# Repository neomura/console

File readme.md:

# neomura/console

Circuit design and shell for home console.

| Link                                         | Description                                        |
| -------------------------------------------- | -------------------------------------------------- |
| [License](./license.md)                      | MIT License.                                       |
| [Circuit Design](./circuit-design/readme.md) | KiCad files and assembly instructions for the PCB. |
| [Shell](./shell/readme.md)                   | OpenSCAD modules for the outer shell.              |

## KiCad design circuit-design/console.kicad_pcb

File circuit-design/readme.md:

# [neomura/console](../readme.md)/Circuit Design

| Link                                                                                               | Description                             |
| -------------------------------------------------------------------------------------------------- | --------------------------------------- |
| [console.pro](./console.pro)                                                                       | KiCAD project.                          |
| [console.sch](./console.sch)                                                                       | KiCAD schematic.                        |
| [console.kicad_pcb](./console.kicad_pcb)                                                           | KiCAD PCB layout.                       |
| [Neomura_Console.lib](./Neomura_Console.lib)                                                       | KiCAD symbol for pad connector.         |
| [Neomura_Console.pretty/BS800L.kicad_mod](./Neomura_Console.pretty/BS800L.kicad_mod)               | KiCAD footprint for power/reset switch. |
| [Neomura_Console.pretty/Pad_Connector.kicad_mod](./Neomura_Console.pretty/Pad_Connector.kicad_mod) | KiCAD footprint for pad connector.      |
| [Neomura_Console.pretty/RCA_Jack.kicad_mod](./Neomura_Console.pretty/RCA_Jack.kicad_mod)           | KiCAD footprint for RCA jack.           |

## Bill of materials

Links are included for reference only and are not endorsements.

| Reference   | Description                                             | Model No.         | Link                                                                                                                                                                                               |
| ----------- | ------------------------------------------------------- | ----------------- | -------------------------------------------------------------------------------------------------------------------------------------------------------------------------------------------------- |
| J1          | Cartridge connector (1x15 2.54mm female pin socket)     | Unknown           | [https://www.aliexpress.com/item/33021040052.html?spm=a2g0s.9042311.0.0.65b74c4dMpBmdG](https://www.aliexpress.com/item/33021040052.html?spm=a2g0s.9042311.0.0.65b74c4dMpBmdG)                     |
| J2          | 2.1mm PCB-mount DC power jack                           | Unknown           | [https://www.bitsbox.co.uk/index.php?main_page=product_info&cPath=225_232&products_id=1697](https://www.bitsbox.co.uk/index.php?main_page=product_info&cPath=225_232&products_id=1697)             |
| J3          | Yellow PCB-mount RCA jack                               | AV-8.4-5 (yellow) | [https://www.aliexpress.com/item/4000661766823.html?spm=a2g0s.9042311.0.0.102e4c4dDtr353](https://www.aliexpress.com/item/4000661766823.html?spm=a2g0s.9042311.0.0.102e4c4dDtr353)                 |
| J4          | White PCB-mount RCA jack                                | AV-8.4-5 (white)  | [https://www.aliexpress.com/item/4000661766823.html?spm=a2g0s.9042311.0.0.102e4c4dDtr353](https://www.aliexpress.com/item/4000661766823.html?spm=a2g0s.9042311.0.0.102e4c4dDtr353)                 |
| J5          | Red PCB-mount RCA jack                                  | AV-8.4-5 (red)    | [https://www.aliexpress.com/item/4000661766823.html?spm=a2g0s.9042311.0.0.102e4c4dDtr353](https://www.aliexpress.com/item/4000661766823.html?spm=a2g0s.9042311.0.0.102e4c4dDtr353)                 |
| J6/J7/J8/J9 | 90-degree SNES controller jack                          | Unknown           | [https://www.aliexpress.com/item/32828768824.html?spm=a2g0s.9042311.0.0.102e4c4dh9cZSi](https://www.aliexpress.com/item/32828768824.html?spm=a2g0s.9042311.0.0.102e4c4dh9cZSi)                     |
| SW1         | 8x8mm latching button                                   | BS800L            | [https://www.amazon.co.uk/gp/product/B01KJHR3W6/ref=ppx_yo_dt_b_asin_title_o01_s00?ie=UTF8&psc=1](https://www.amazon.co.uk/gp/product/B01KJHR3W6/ref=ppx_yo_dt_b_asin_title_o01_s00?ie=UTF8&psc=1) |
| SW2         | 8x8mm momentary button                                  | Unknown           | [https://www.amazon.co.uk/gp/product/B00TX5K07G/ref=ppx_yo_dt_b_asin_title_o00_s00?ie=UTF8&psc=1](https://www.amazon.co.uk/gp/product/B00TX5K07G/ref=ppx_yo_dt_b_asin_title_o00_s00?ie=UTF8&psc=1) |
| R1          | 4.7K resistor                                           | Unknown           | [https://www.bitsbox.co.uk/index.php?main_page=product_info&cPath=83_84_85&products_id=2561](https://www.bitsbox.co.uk/index.php?main_page=product_info&cPath=83_84_85&products_id=2561)           |
| D1          | Green 5x2x8 rectangular LED                             | Unknown           | [https://www.bitsbox.co.uk/index.php?main_page=product_info&cPath=172_177&products_id=1343](https://www.bitsbox.co.uk/index.php?main_page=product_info&cPath=172_177&products_id=1343)             |

A USB A to 2.1mm DC 5V cable such as [https://www.amazon.co.uk/gp/product/B07SR1SGXQ/ref=ppx_yo_dt_b_asin_title_o05_s00?ie=UTF8&psc=1](https://www.amazon.co.uk/gp/product/B07SR1SGXQ/ref=ppx_yo_dt_b_asin_title_o05_s00?ie=UTF8&psc=1) can be used to power the console from a USB power supply.

9.5x4mm self-adhestive feet such as [https://www.bitsbox.co.uk/index.php?main_page=product_info&cPath=185_190&products_id=1418](https://www.bitsbox.co.uk/index.php?main_page=product_info&cPath=185_190&products_id=1418) can be applied to the pockets in the unside of the shell.

### Possible substitutions

#### SW2

SW2 has identical external dimensions to SW1.  It is possible to convert a BS800L to a momentary switch as the momentary variant appears to be somewhat uncommon:

- Use a spudger or pair of tweasers to prise the tabs on opposite sides away and lift the top half of the body away - these tabs are usually white if the bottom half is black or vice versa.
- The blue plunger should now lift out.  Note that there is a small spring underneath it, and a metal contact on either side of it.  These may fall off.
- At the bottom of the bottom half of the body is a small piece of bent wire which is responsible for the latching motion (you can see this through the square cutout in the bottom of the switch).  You should be able to remove this using tweasers.
- Replace the blue plunger, putting the spring back in and pressing the metal contacts back on if they fell off.
- Replace the top half of the body.  The tabs should click back into place.

The button should now press like before, but not latch.  You can check that the switch still works using a multimeter, looking from the bottom:

```
.-----.
|1 3 2|
|   []|
|6 4 5|
'-----'
```

When the switch **is not** pressed, leads 1 and 3, and 6 and 4 **should** be connected.  Leads 3 and 2, and 4 and 5 **should not** be connected.

When the switch **is** pressed, leads 3 and 2, and 4 and 5 **should** be connected.  Leads 1 and 3, and 6 and 4 **should not** be connected.

SW2 could also be omitted entirely at the cost of losing reset functionality (removal of the hole in the top half of the shell is recommended if this is done).

#### D1

The LED can be replaced or omitted entirely - just ensure that R1 is adjusted (or omitted) as appropriate.  Removal of the hole in the top half of the shell is recommended if the LED is omitted.

## Assembly instructions

- Solder R1 and J1, and clip leads.  Ensure that J1's underside is flat against the PCB (no gap, and upright) otherwise the cartridge may not fit.
- Place the top half of the shell upside down.
- Place J2, J3, J4, J5, J6, J7, J8, J9 and D1 into their respective cavities in the top half of the shell.
- Place the PCB logo side down onto the leads of the placed components.
- Solder J2, J3, J4, J5, J6, J7, J8, J9 and D1, and clip leads.
- Press-fit the bottom half of the shell in place.

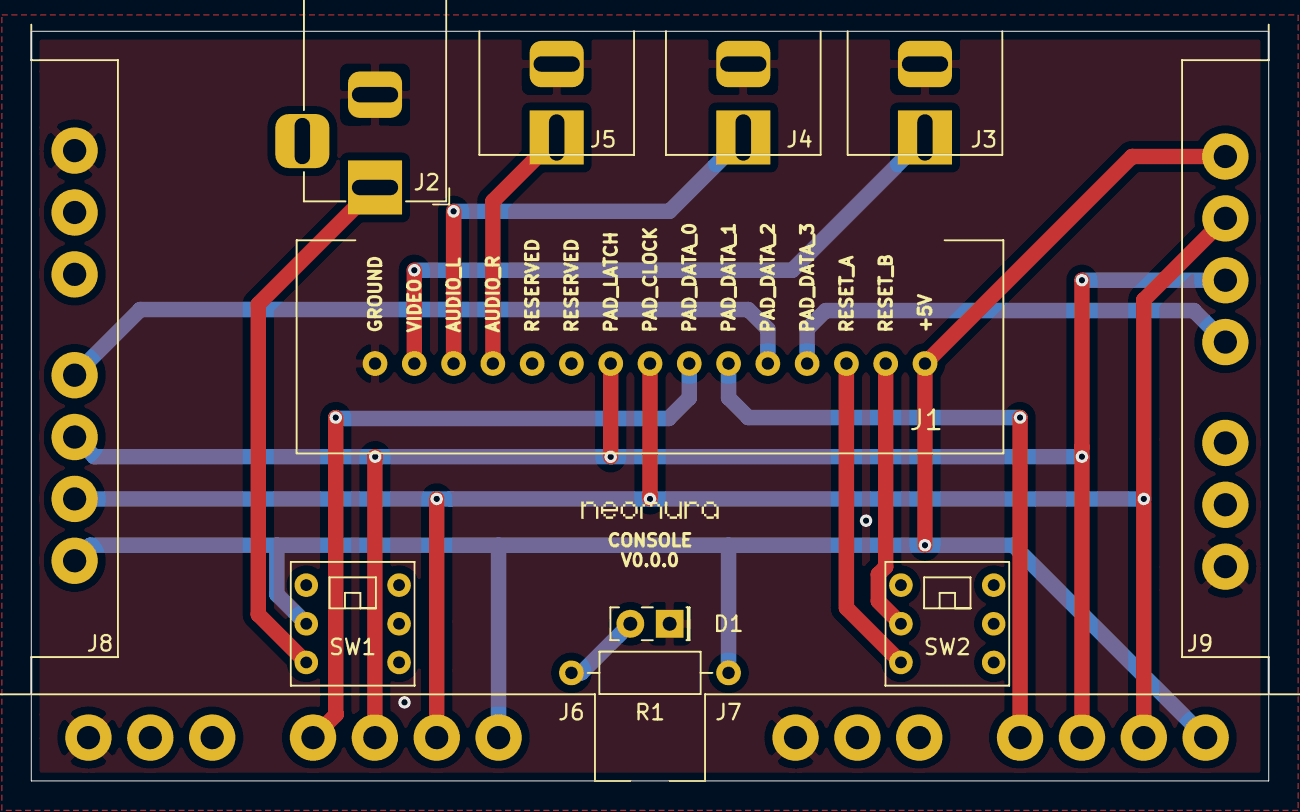
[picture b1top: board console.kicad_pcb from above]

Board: 2 copper layers, 80.0 x 48.5 mm, 14 parts (0 on the bottom side), 15 nets.

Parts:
D1: LED; LED_Rectangular_W5.0mm_H2.0mm
J1: CARTRIDGE; Slot-Vertical
J2: POWER; BarrelJack_Horizontal
J3: VIDEO (YELLOW); RCA_Jack
J4: AUDIO (WHITE); RCA_Jack
J5: AUDIO (RED); RCA_Jack
J6: PAD 0; Pad_Connector
J7: PAD 1; Pad_Connector
J8: PAD 2; Pad_Connector
J9: PAD 3; Pad_Connector
R1: 240R; R_Axial_DIN0207_L6.3mm_D2.5mm_P10.16mm_Horizontal
Ref**: Val**; Front-Silkscreen
SW1: POWER_SW; BS800L
SW2: RESET_SW; BS800L

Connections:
+5V: J1.15, J6.1, J7.1, J8.1, J9.1, R1.2, SW1.6
AUDIO_L: J1.3, J4.1
AUDIO_R: J1.4, J5.1
GND: D1.1, J1.1, J2.2, J3.2, J4.2, J5.2, J6.7, J7.7, J8.7, J9.7
unnamed: D1.2, R1.1
unnamed: J2.1, SW1.5
PAD_CLOCK: J1.8, J6.2, J7.2, J8.2, J9.2
PAD_DATA_0: J1.9, J6.4
PAD_DATA_1: J1.10, J7.4
PAD_DATA_2: J1.11, J8.4
PAD_DATA_3: J1.12, J9.4
PAD_LATCH: J1.7, J6.3, J7.3, J8.3, J9.3
RESET_A: J1.13, SW2.5
RESET_B: J1.14, SW2.6
VIDEO: J1.2, J3.1

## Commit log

2021-02-10 Update submodules.
2021-02-10 Initial commit.
2021-02-13 Add PCB.
2021-02-13 Fix typo and improve clarity.
2021-02-13 Fix sikscreen positioning.
2021-02-13 Update export settings.
2021-02-13 Add missing audio via.
2021-02-13 Add initial drafts of power/reset buttons.
2021-02-13 Fix description.
2021-02-13 Correct measurements.
2021-02-13 Rotate buttons.
2021-02-13 Fix incorect sizing of buttons.
2021-02-13 Add a surround to guide button caps down the button.
2021-02-13 Build most of the shell.
2021-02-13 Fix alignment of DC jack and remove need for slots on back edge.
2021-02-14 Turn unsplit into a module.
2021-02-15 Fix regression caused by submodule update.
2021-02-16 Increase DC jack sides.
2021-02-16 Add foot.
2021-02-16 Add missing cutouts for pad connector terminals.
2021-02-16 Make room for feet.
2021-02-16 Add module for drawing a badge along the edge of the console.
2021-02-16 Fix cutaway for terminals being twice intended size.
2021-02-16 Slightly enlarge DC jack.
2021-02-16 Define pad positions for DC jack.
2021-02-16 Slightly enlarge RCA jacks.
2021-02-17 Update submodules/neomura/cartridge commit hash to a232597
2021-02-19 Redesign to support new cartridge connector.
2021-02-19 Slightly increase pad connector height.
2021-02-19 Redesign feet to use off the shelf components.
2021-02-19 Add dimensions for labels.
2021-02-19 Increase button tolerance.
2021-02-19 Rotate badges.
2021-02-19 Add measurements for retaining pegs.
2021-02-19 Adjust RCA jack position.
2021-02-19 Define locations of bottom pockets required by RCA jacks.
2021-02-19 Update readme.
2021-02-20 Remove unnecessary via.
2021-02-20 Update documentation.
2021-02-20 Update BOM.
2021-03-10 Update submodules/neomura/cartridge commit hash to 89bc0f9
2021-03-10 Final revisions.
2021-03-21 Fix the LED being offset.
2021-03-21 Add version badges.
2021-03-21 Increase the sizes of buttons and LEDs for a better fit.
2021-03-23 Reduce overhang.
2021-03-27 Reduce peg height. This makes them less likely to break without losing any friction fit quality.
2021-04-13 Decrease LED current.
2021-04-16 Begin redesigning to take NES controllers.
2021-04-16 Reorder jacks.
2021-04-16 Continue redesign.
2021-04-16 Redesign buttons.
2021-04-16 Update submodules/neomura/cartridge commit hash to b22c4fe
